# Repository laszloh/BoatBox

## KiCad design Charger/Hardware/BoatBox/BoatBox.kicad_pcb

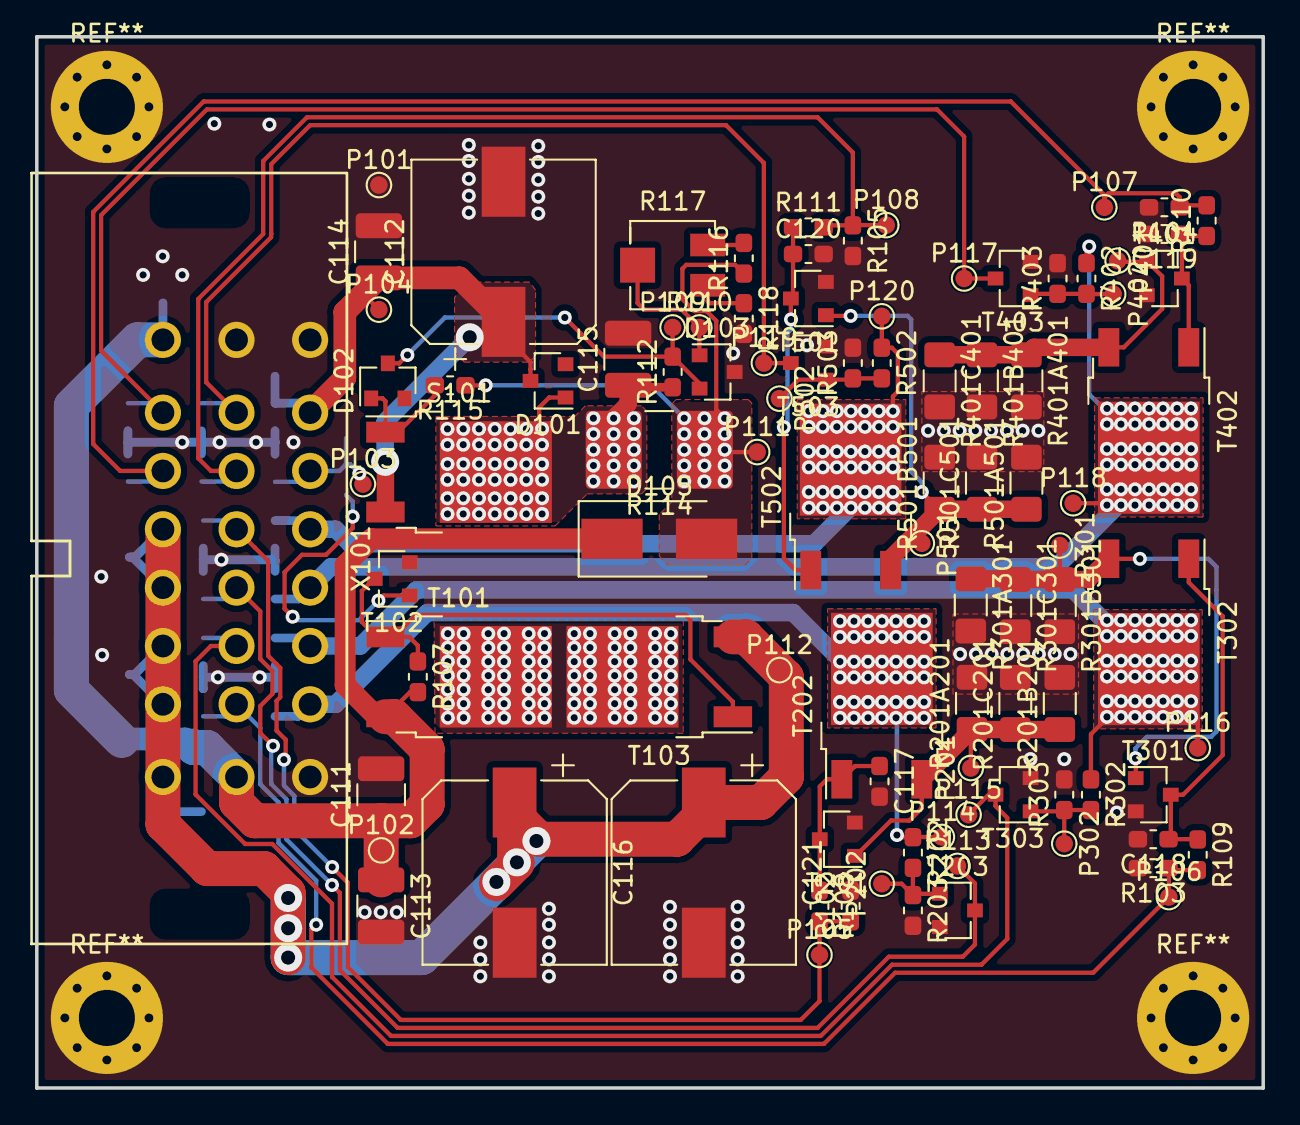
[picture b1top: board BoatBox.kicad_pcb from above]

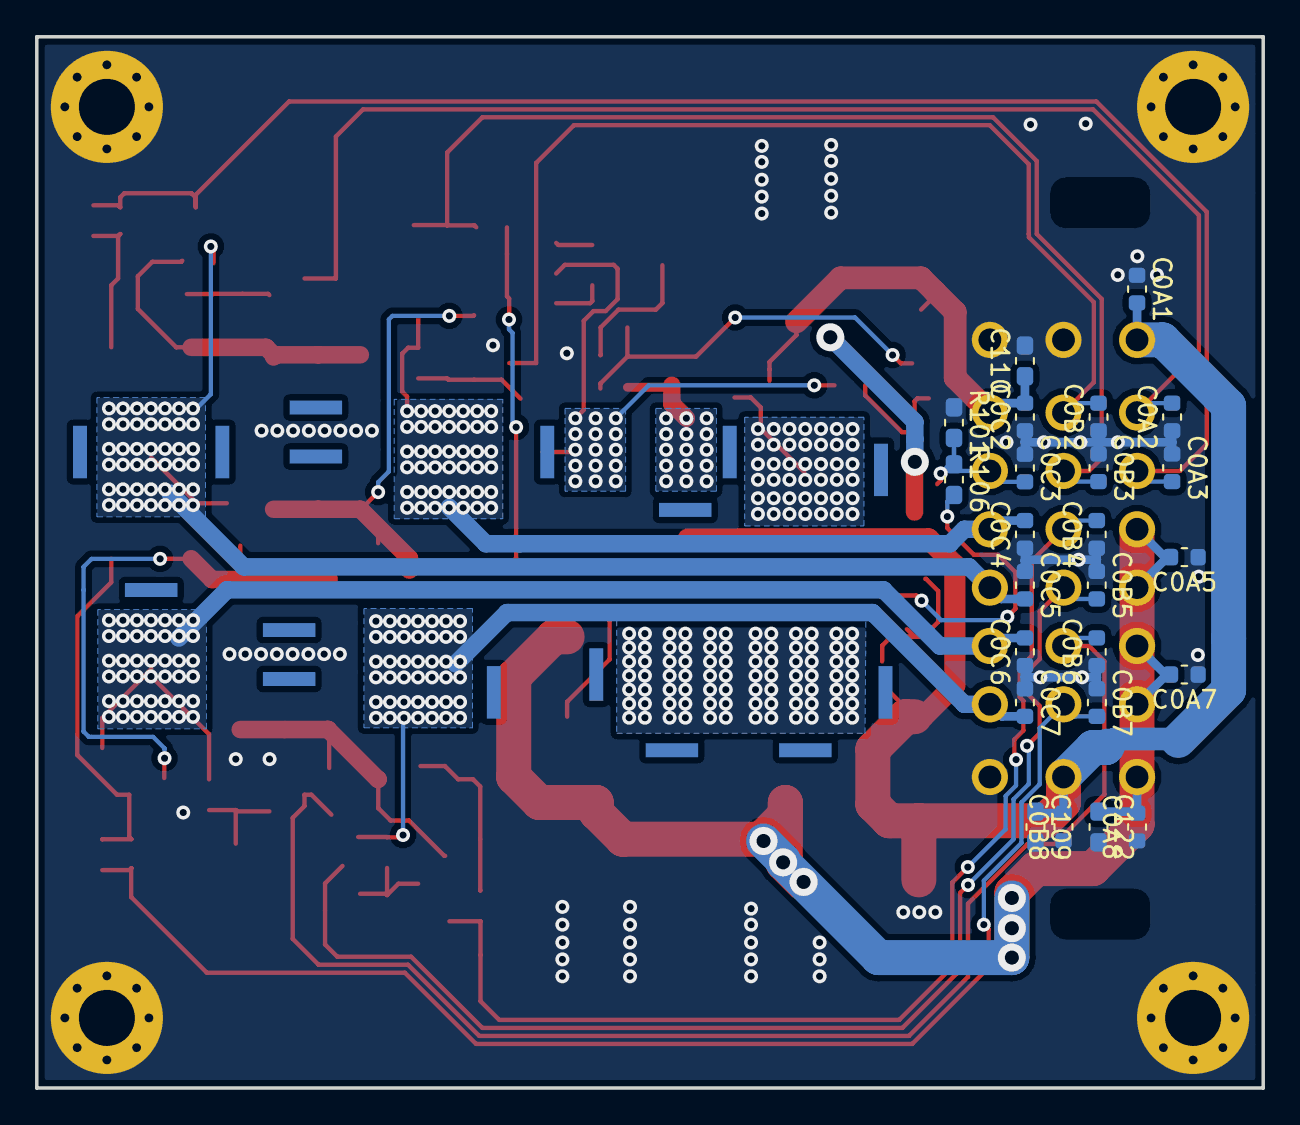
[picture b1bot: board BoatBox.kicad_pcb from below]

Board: 2 copper layers, 70.0 x 60.0 mm, 119 parts (24 on the bottom side), 39 nets.

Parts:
C0A1, C0A2, C0A3, C0A5, C0A7, C0A8, C0B2, C0B3, C0B4, C0B5, C0B6, C0B7, C0B8, C0C2, C0C3, C0C4, C0C5, C0C6, C0C7: 4.7n; C_0603_1608Metric
C109, C110, C122: 100n; C_0603_1608Metric_Pad1.05x0.95mm_HandSolder
C111, C113, C114, C115: 10u; C_1210_3225Metric_Pad1.42x2.65mm_HandSolder
C112, C116, C121: 270u; CP_Elec_10x10
C117, C118, C119, C120: 68n; C_0603_1608Metric_Pad1.05x0.95mm_HandSolder
D101, D102: BAS16; D_SOT-23_ANK
D103: NCP431; SOT-23
D105: MBRS360T3G; D_SMB_Handsoldering
P101, P102, P103, P104, P105, P106, P107, P108, P109, P110, P111, P112, P113, P114, P115, P116, P117, P118, P119, P120, P201, P202, P301, P302, P401, P402, P501, P502: TestPoint; TestPoint_Pad_D1.0mm
R101, R107: 10k; R_0603_1608Metric_Pad1.05x0.95mm_HandSolder
R102, R103, R104, R105, R106, R108, R109, R110, R111: 46.4k; R_0603_1608Metric_Pad1.05x0.95mm_HandSolder
R112, R115: 1k; R_0603_1608Metric_Pad1.05x0.95mm_HandSolder
R114: 2.7R; R_2816_7142Metric_Pad3.20x4.45mm_HandSolder
R116, R118: 50m; R_0603_1608Metric_Pad1.05x0.95mm_HandSolder
R117: 10k; Potentiometer_Cemet_23A_Horizontal
R201A201, R201B201, R201C201, R301A301, R301B301, R301C301, R401A401, R401B401, R401C401, R501A501, R501B501, R501C501: 1R; R_1206_3216Metric_Pad1.42x1.75mm_HandSolder
R202, R302, R402, R502: 100k; R_0603_1608Metric_Pad1.05x0.95mm_HandSolder
R203, R303, R403, R503: 470k; R_0603_1608Metric_Pad1.05x0.95mm_HandSolder
S101: LM317; TO-252-2
T101, T103: IRFR5505PBF; TO-252-2
T102, T203, T303, T403, T503: BSS138; SOT-23
T201, T301, T401, T501: BC847; SOT-23
T202, T302, T402, T502: IPD50R380CE; TO-252-2
X101: HCCPHPE24BKA90F

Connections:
/A_S_DIAG1: C0B5.2, P113.1, T203.3, X101.13
/A_S_DIAG2: C0B6.2, P115.1, T303.3, X101.14
/A_S_DIAG3: C0A2.2, P117.1, T403.3, X101.2
/A_S_DIAG4: C0B2.2, P119.1, T503.3, X101.10
/A_T_OUT1: C0C7.2, P114.1, R202.1, T202.2, X101.23
/A_T_OUT2: C0C6.2, P116.1, R302.1, T302.2, X101.22
/A_T_OUT3: C0C5.2, P118.1, R402.1, T402.2, X101.21
/A_T_OUT4: C0C4.2, P120.1, R502.1, T502.2, X101.20
/E_S_CTL1: C0B4.2, P105.1, R102.1, R108.2, X101.12
/E_S_CTL2: C0B7.2, P106.1, R103.1, R109.2, X101.15
/E_S_CTL3: C0A3.2, P107.1, R104.1, R110.2, X101.3
/E_S_CTL4: C0B3.2, P108.1, R105.1, R111.2, X101.11
/E_S_RLY: C0C3.2, P103.1, R101.2, R106.1, X101.19
/LSS 1/ctrl: C117.1, R108.1, T201.3, T202.1
/LSS 2/ctrl: C118.1, R109.1, T301.3, T302.1
/LSS 3/ctrl: C119.1, R110.1, T401.3, T402.1
/LSS 4/ctrl: C120.1, R111.1, T501.3, T502.1
/U_U_CHRG: C0C2.2, C110.1, C112.1, C114.1, D101.1, P104.1, S101.3, X101.18
GND: C0A1.1, C0A2.1, C0A3.1, C0A5.1, C0A7.1, C0A8.1, C0B2.1, C0B3.1, C0B4.1, C0B5.1, C0B6.1, C0B7.1, C0B8.1, C0C2.1, C0C3.1, C0C4.1, C0C5.1, C0C6.1, C0C7.1, C109.2, C110.2, C111.2, C112.2, C113.2, C114.2, C115.2, C116.2, C117.2, C118.2, C119.2, C120.2, C121.2, C122.2, D103.3, P101.1, R101.1, R102.2, R103.2, R104.2, R105.2, R118.2, R201A201.2, R201B201.2, R201C201.2, R203.2, R301A301.2, R301B301.2, R301C301.2, R303.2, R401A401.2, R401B401.2, R401C401.2, R403.2, R501A501.2, R501B501.2, R501C501.2, R503.2, T102.2, T201.2, T203.2, T301.2, T303.2, T401.2, T403.2, T501.2, T503.2, X101.9, X101.17, X101.24
unnamed: C115.1, D101.2, R112.1, R114.2, S101.2
unnamed: D102.1, D103.2, P109.1, R112.2
unnamed: D102.2, R115.2, S101.1
unnamed: D103.1, P110.1, R117.2
unnamed: D105.2, P111.1, R114.1, R115.1, R116.1
unnamed: P201.1, R201A201.1, R201B201.1, R201C201.1, T201.1, T202.3
unnamed: P202.1, R202.2, R203.1, T203.1
unnamed: P301.1, R301A301.1, R301B301.1, R301C301.1, T301.1, T302.3
unnamed: P302.1, R302.2, R303.1, T303.1
unnamed: P401.1, R401A401.1, R401B401.1, R401C401.1, T401.1, T402.3
unnamed: P402.1, R402.2, R403.1, T403.1
unnamed: P501.1, R501A501.1, R501B501.1, R501C501.1, T501.1, T502.3
unnamed: P502.1, R502.2, R503.1, T503.1
unnamed: R106.2, T102.1
unnamed: R107.1, T101.1, T102.3, T103.1
unnamed: R116.2, R117.1
unnamed: R117.3, R118.1
unnamed: T101.2, T103.2
UBD: C0A1.2, C0B8.2, C109.1, C111.1, C113.1, D105.1, P102.1, R107.2, T101.3, X101.1, X101.16
UBR: C0A5.2, C0A7.2, C0A8.2, C116.1, C121.1, C122.1, P112.1, T103.3, X101.4, X101.5, X101.6, X101.7, X101.8

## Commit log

2018-10-12 First import of project
    The schematic is almost finished.
    ToDo:
    - Assign footprints
    - Define board size, controll unit housing size
    - Create the Layout
2018-10-12 Layout update
    Still in work
2018-10-12 Pin swap A1 and B1
    Swapped to ease the routing of GND and UBD.
2018-10-31 WIP commit
    squash after finish.
2019-01-18 Start to create the new pcb
    Main features in this revision shall be:
    -) 3D printed housing
    -) raised aluminium inlay for heat transfer
2019-01-25 WIP commit of new layout
    squash after finish
2019-01-26 New layout finished
    Started work on the 3D printed housing. The cooling bench will be created
    as an inlay made of 4mm steel (or aluminium).
